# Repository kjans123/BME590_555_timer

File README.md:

# BME590_555_timer
https://www.instructables.com/id/555-Timer/#step6

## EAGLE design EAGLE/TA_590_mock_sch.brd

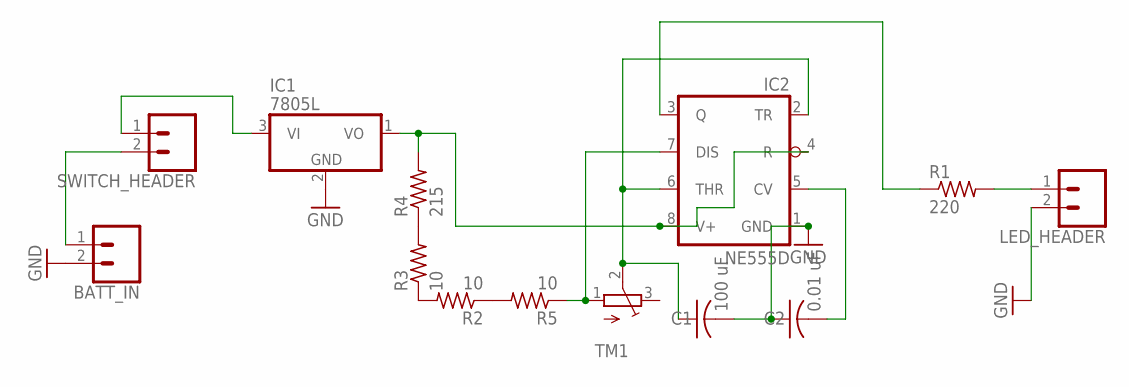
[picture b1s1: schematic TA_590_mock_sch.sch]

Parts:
BATT_IN: CONN_02; 1X02
C1: 100 uF; C0805
C2: 0.01 uF; C0805
IC1: 7805L; TO92
IC2: NE555D; SO08
LED_HEADER: CONN_02; 1X02
R1: 220; R0805
R2, R3, R5: 10; R0805
R4: 215; R0805
SWITCH_HEADER: CONN_02; 1X02
TM1: TRIMPOTTC33X; TC33X

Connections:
GND: BATT_IN.2, C1.2, C2.1, IC1.2 (GND), IC2.1 (GND), LED_HEADER.2
unnamed: BATT_IN.1, SWITCH_HEADER.2
unnamed: IC1.3 (VI), SWITCH_HEADER.1
unnamed: R2.1, R5.2
unnamed: R3.2, R4.1
unnamed: R2.2, R3.1
unnamed: IC2.3 (Q), R1.1
unnamed: IC2.7 (DIS), R5.1, TM1.1 (A)
unnamed: C1.1, IC2.2 (TR), IC2.6 (THR), TM1.2 (S)
unnamed: C2.2, IC2.5 (CV)
unnamed: LED_HEADER.1, R1.2
PWR: IC1.1 (VO), IC2.4 (R), IC2.8 (V+), R4.2

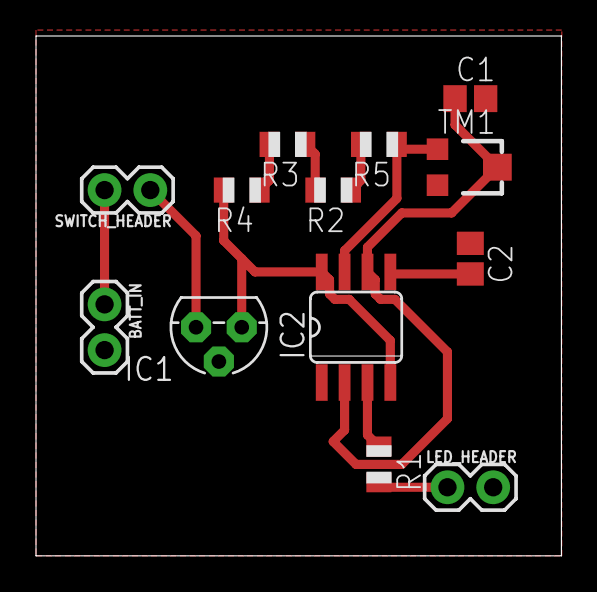
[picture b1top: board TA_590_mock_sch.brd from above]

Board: 2 copper layers, 29.2 x 28.9 mm, 13 parts (0 on the bottom side), 12 nets.

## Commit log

2019-01-13 commit for py_solver.py file
2019-01-13 example video of working 555 circuit
2019-01-13 reformat of video
2019-01-13 circ_diagram and pinout push
2019-01-14 draft of eagle board and schem
2019-01-14 moved Eagle files
2019-01-14 edited polygon
2019-01-14 re-push of EAGLE schem file to reflect polygon edit
2019-01-14 ubuntu subsytem did not see file update
2019-04-04 save

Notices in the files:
parts and their libraries:
SparkFun-Connectors: Licensing: Creative Commons ShareAlike 4.0 International - https://creativecommons.org/licenses/by-sa/4.0
